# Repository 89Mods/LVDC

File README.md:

# LVDC
Replica of the [Launch Vehicle Digital Computer](https://www.ibiblio.org/apollo/LVDC.html) using 74-series logic. This projects only aims to keep the CPU Architecture binary-compatible with the original. Implementation details, IO Peripherals and Software are all originally created by me. This is party due to the fact that detailed hardware descriptions (i.e. schematics) are not as abundant for the LVDC as for the AGC, but also because this project doubled as a challenge to myself to implement such an odd instruction set, but using every trick I’ve learned from my years of engineering integrated circuit layouts. It turns out that applying nanoscale engineering tricks to a macroscale discrete logic build can work out quite well. The clock speed of this computer is 2.5MHz, but it can probably go faster.

This LVDC is accurate to the original in the sense that it executes the same instructions that function the exact same, has the same memory layout (including special locations like HOP save and MQ) and can execute snippets of original LVDC code.

The differences are:
  - This computer is parallel and not bit-serial, and is also microcoded
  - It is implemented using 74-series logic and not discrete transistors (I wish to be able to take it with me to events, so it couldn’t get too big)
  - Everything hooked up to the PIO (IO read/write) instruction is my own invention, with the exception of the the interrupt latch clear IO location, which it shares with the original LVDC
  - Instruction cycles times are much faster, probably on an order of magnitude or more
  - The hardware multiply/divide circuitry (as designed so far) does NOT share the inacuracies in low-order bits as the original LVDC, instead always producing the 100% correct result

Infact, I took the most liberties with the IO Card, which contains various modern components hooked into the CPU’s IO Bus. Its mostly a random mashup of things I thought would be cool (there is even a Commodore SID replica in there) to demonstrate the computer with.

The most significant addition is that of a front panel (the original LVDC was an embedded device with no user interface) which is a bit like a DSKY, but stripped down and only capable of displaying in hexadecimal. The panel is optional. I can be safely removed and the computer used as a true embedded device.

Software wise, things are still WiP. Two ROMs provide just enough storage for a small bootloader to initialize the entire SRAM from a flash IC. Sadly, core memory is far too bulky and expensive, so this will have to do. I created a mini-OS for this system that allows a user to control the computer by typing in commands consisting of a Noun and Verb into the keypad.

**Known Issues:**
  - The HOP Save feature is bugged. The Instruction Pointer in the stored value is off by one. Trying to return with it will return execution to the transfer or HOP instruction that started the subroutine call, not the one following it, triggering an infinite loop. Fixed for now in software by modifying the saved value before return.
  - While all schematic files have been updated with fixes to additional problems discovered post-production, the schematic layout for the Control board still need to be redone.
  - The EXM instruction has only been minimally tested because I don’t understand how it is useful (thing takes up half a dozen ICs just to handle weird edge cases caused by it and I’m still left scratching my head on how I’m supposed to use it).
  - The hardware multiply/divide functionality has yet to be physically implemented. In `LVDC.circ` you can see that I have designed it, but I’ve yet to translate this to a PCB design because I couldn’t get it made yet anyways (its the most expensive part of the whole computer).
  - The interrupt logic sometimes does not reset properly and I don’t understand why

# Repository Structure

`LVDC.circ` is where I prototyped the logic design using Logisim Evolution, but it is quite bugged and now far outdated.

`microcode_gen.c` is the C program that spits out the raw binary images for the microcode ROMs from a more high-level description.

`KiCad` is where the schematics and PCB layouts live. Related to this is `CPLD`, which holds the HDL code for the CPLD on the GPIO PCB.

`Bench` is the result of using [KiCadVerilog](https://github.com/89Mods/KiCadVerilog) to automatically extract Verilog netlists out of the KiCad schematic files and using them to build a simulation of the computer for verification purposes before starting physical production. This is quite a novel approach and I used it here for the first time.

`behavioral` contains a Behavioral Verilog model of the LVDC I used as a starting point. It is incredibly inaccurate as I have not updated it in same time.

`Programs` contains the software I’m writing for this computer. Currently just the Bootloader source and the WiP mini-OS mentioned earlier. [My fork of the AS Macroassembler](https://github.com/AvalonSemiconductors/asl-avalonsemi/) has support for the LVDC, and this is used to assemble all LVDC code in this directory.

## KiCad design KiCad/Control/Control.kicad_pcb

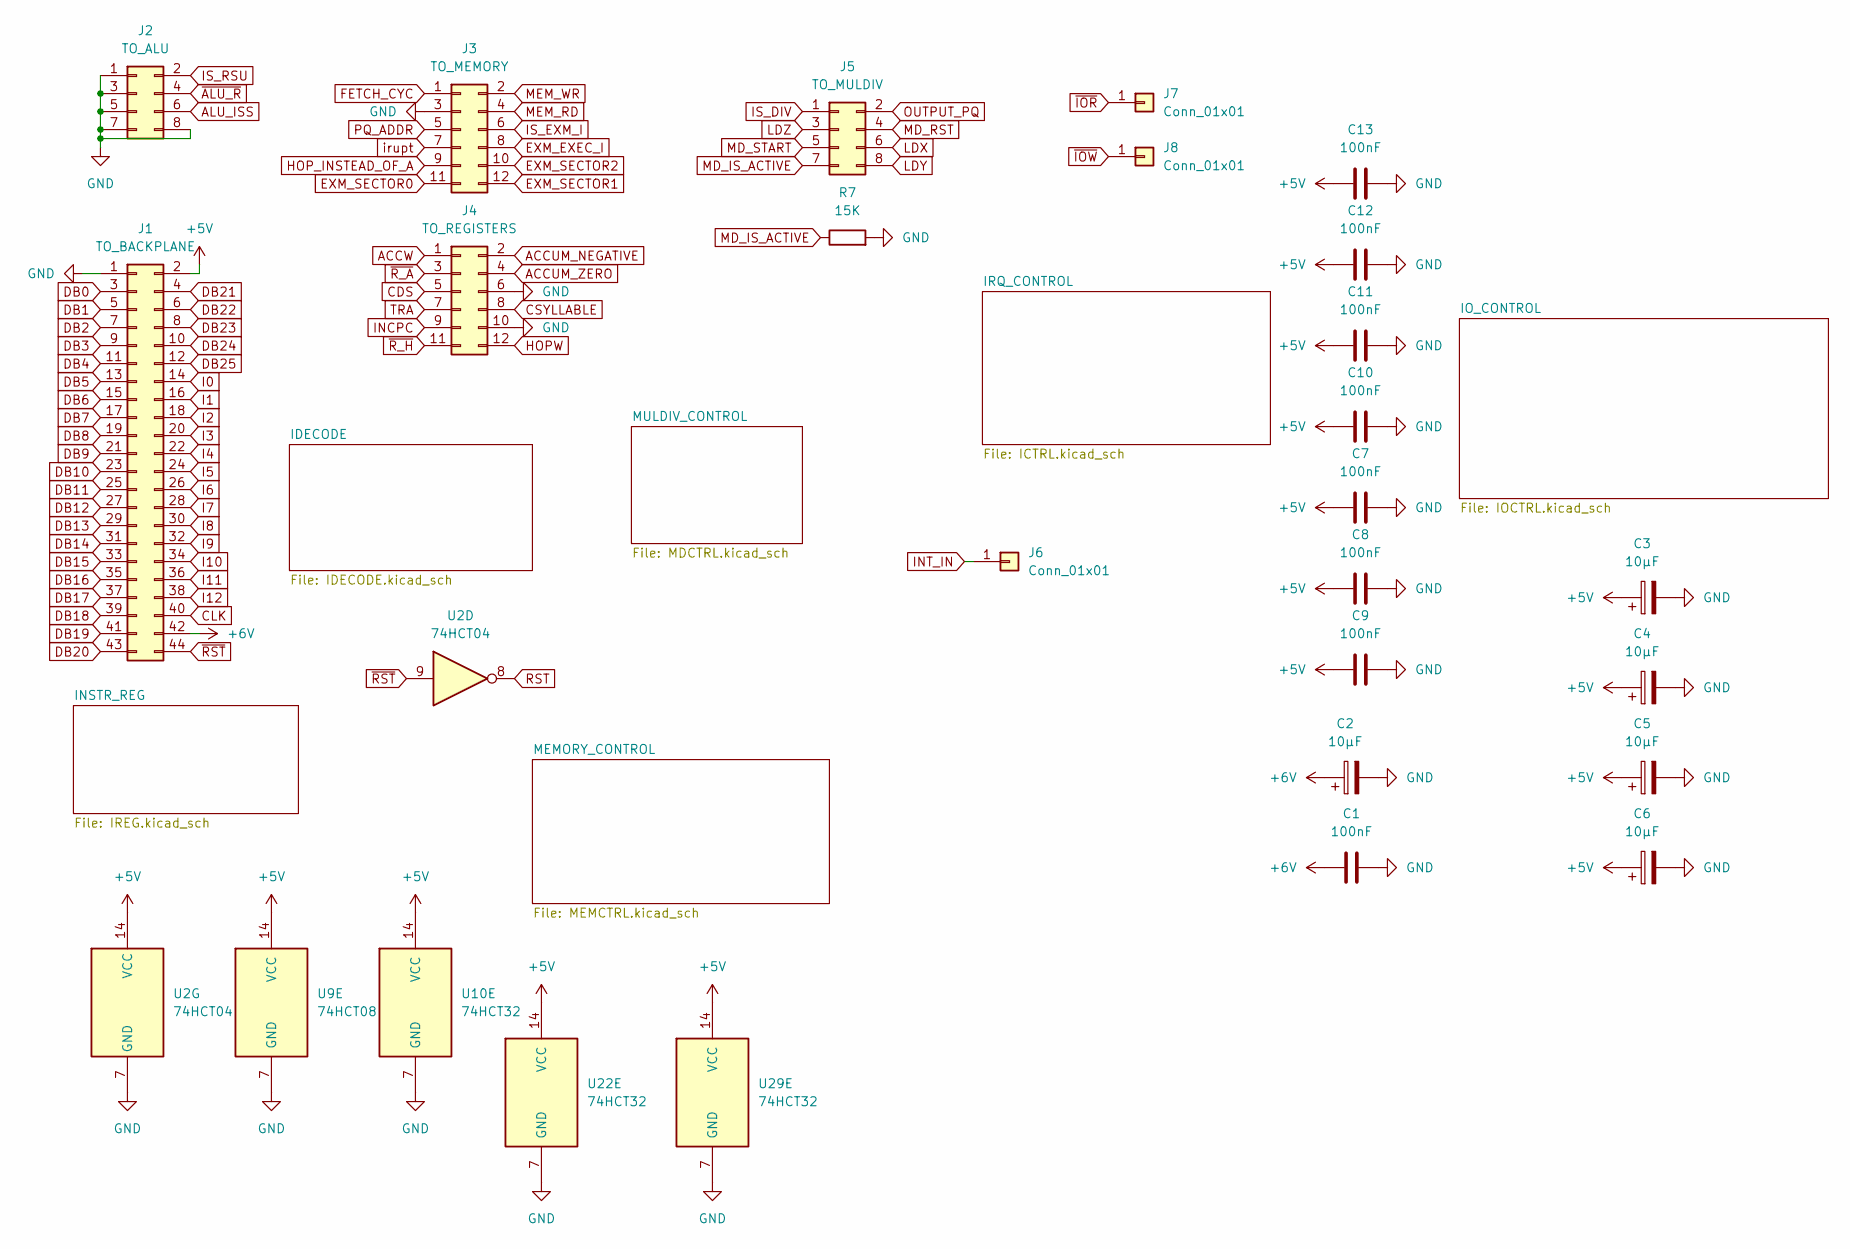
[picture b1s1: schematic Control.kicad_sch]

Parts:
C1, C7, C8, C9, C10, C11, C12, C13: 100nF; C_0805_2012Metric_Pad1.18x1.45mm_HandSolder
C2, C3, C4, C5, C6: 10µF; CP_Radial_D4.0mm_P2.00mm
J1: TO_BACKPLANE; PinHeader_2x22_P2.54mm_Vertical
J2: TO_ALU; PinHeader_2x04_P2.54mm_Vertical
J3: TO_MEMORY; PinHeader_2x06_P2.54mm_Vertical
J4: TO_REGISTERS; PinHeader_2x06_P2.54mm_Vertical
J5: TO_MULDIV; PinHeader_2x04_P2.54mm_Vertical
J6, J7, J8: Conn_01x01; PinHeader_1x01_P2.54mm_Vertical
R7: 15K; R_1206_3216Metric_Pad1.30x1.75mm_HandSolder
U2: 74HCT04; SO-14_3.9x8.65mm_P1.27mm
U9: 74HCT08; SO-14_3.9x8.65mm_P1.27mm
U10, U22, U29: 74HCT32; SO-14_3.9x8.65mm_P1.27mm

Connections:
+5V: C3.1, C4.1, C5.1, C6.1, C7.1, C8.1, C9.1, C10.1, C11.1, C12.1, C13.1, J1.2, U2.14 (VCC), U9.14 (VCC), U10.14 (VCC), U22.14 (VCC), U29.14 (VCC); also elsewhere on the board
+6V: C1.1, C2.1, J1.42; also elsewhere on the board
ACCUM_NEGATIVE: J4.2; also elsewhere on the board
ACCUM_ZERO: J4.4; also elsewhere on the board
ACCW: J4.1; also elsewhere on the board
ALU_ISS: J2.6; also elsewhere on the board
CDS: J4.5; also elsewhere on the board
CLK: J1.40; also elsewhere on the board
CSYLLABLE: J4.8; also elsewhere on the board
DB0: J1.3; also elsewhere on the board
DB1: J1.5; also elsewhere on the board
DB2: J1.7; also elsewhere on the board
DB3: J1.9; also elsewhere on the board
DB4: J1.11; also elsewhere on the board
DB5: J1.13; also elsewhere on the board
DB6: J1.15; also elsewhere on the board
DB7: J1.17; also elsewhere on the board
DB8: J1.19; also elsewhere on the board
DB9: J1.21; also elsewhere on the board
DB10: J1.23; also elsewhere on the board
DB11: J1.25; also elsewhere on the board
DB12: J1.27; also elsewhere on the board
DB13: J1.29; also elsewhere on the board
DB14: J1.31; also elsewhere on the board
DB15: J1.33; also elsewhere on the board
DB16: J1.35; also elsewhere on the board
DB17: J1.37; also elsewhere on the board
DB18: J1.39; also elsewhere on the board
DB19: J1.41; also elsewhere on the board
DB20: J1.43; also elsewhere on the board
DB21: J1.4; also elsewhere on the board
DB22: J1.6; also elsewhere on the board
DB23: J1.8; also elsewhere on the board
DB24: J1.10; also elsewhere on the board
DB25: J1.12; also elsewhere on the board
EXM_EXEC_I: J3.8; also elsewhere on the board
EXM_SECTOR0: J3.11; also elsewhere on the board
EXM_SECTOR1: J3.12; also elsewhere on the board
EXM_SECTOR2: J3.10; also elsewhere on the board
FETCH_CYC: J3.1; also elsewhere on the board
GND: C1.2, C2.2, C3.2, C4.2, C5.2, C6.2, C7.2, C8.2, C9.2, C10.2, C11.2, C12.2, C13.2, J1.1, J2.1, J2.3, J2.5, J2.7, J2.8, J3.3, J4.6, J4.10, R7.2, U2.7 (GND), U9.7 (GND), U10.7 (GND), U22.7 (GND), U29.7 (GND); also elsewhere on the board
HOPW: J4.12; also elsewhere on the board
HOP_INSTEAD_OF_A: J3.9; also elsewhere on the board
I0: J1.14; also elsewhere on the board
I1: J1.16; also elsewhere on the board
I2: J1.18; also elsewhere on the board
I3: J1.20; also elsewhere on the board
I4: J1.22; also elsewhere on the board
I5: J1.24; also elsewhere on the board
I6: J1.26; also elsewhere on the board
I7: J1.28; also elsewhere on the board
I8: J1.30; also elsewhere on the board
I9: J1.32; also elsewhere on the board
I10: J1.34; also elsewhere on the board
I11: J1.36; also elsewhere on the board
I12: J1.38; also elsewhere on the board
INCPC: J4.9; also elsewhere on the board
INT_IN: J6.1; also elsewhere on the board
IS_DIV: J5.1; also elsewhere on the board
IS_EXM_I: J3.6; also elsewhere on the board
IS_RSU: J2.2; also elsewhere on the board
LDX: J5.6; also elsewhere on the board
LDY: J5.8; also elsewhere on the board
LDZ: J5.3; also elsewhere on the board
MD_IS_ACTIVE: J5.7, R7.1; also elsewhere on the board
MD_RST: J5.4; also elsewhere on the board
MD_START: J5.5; also elsewhere on the board
MEM_RD: J3.4; also elsewhere on the board
MEM_WR: J3.2; also elsewhere on the board
OUTPUT_PQ: J5.2; also elsewhere on the board
PQ_ADDR: J3.5; also elsewhere on the board
RST: U2.8; also elsewhere on the board
TRA: J4.7; also elsewhere on the board
irupt: J3.7; also elsewhere on the board
~ALU_R: J2.4; also elsewhere on the board
~IOR: J7.1; also elsewhere on the board
~IOW: J8.1; also elsewhere on the board
~RST: J1.44, U2.9; also elsewhere on the board
~R_A: J4.3; also elsewhere on the board
~R_H: J4.11; also elsewhere on the board

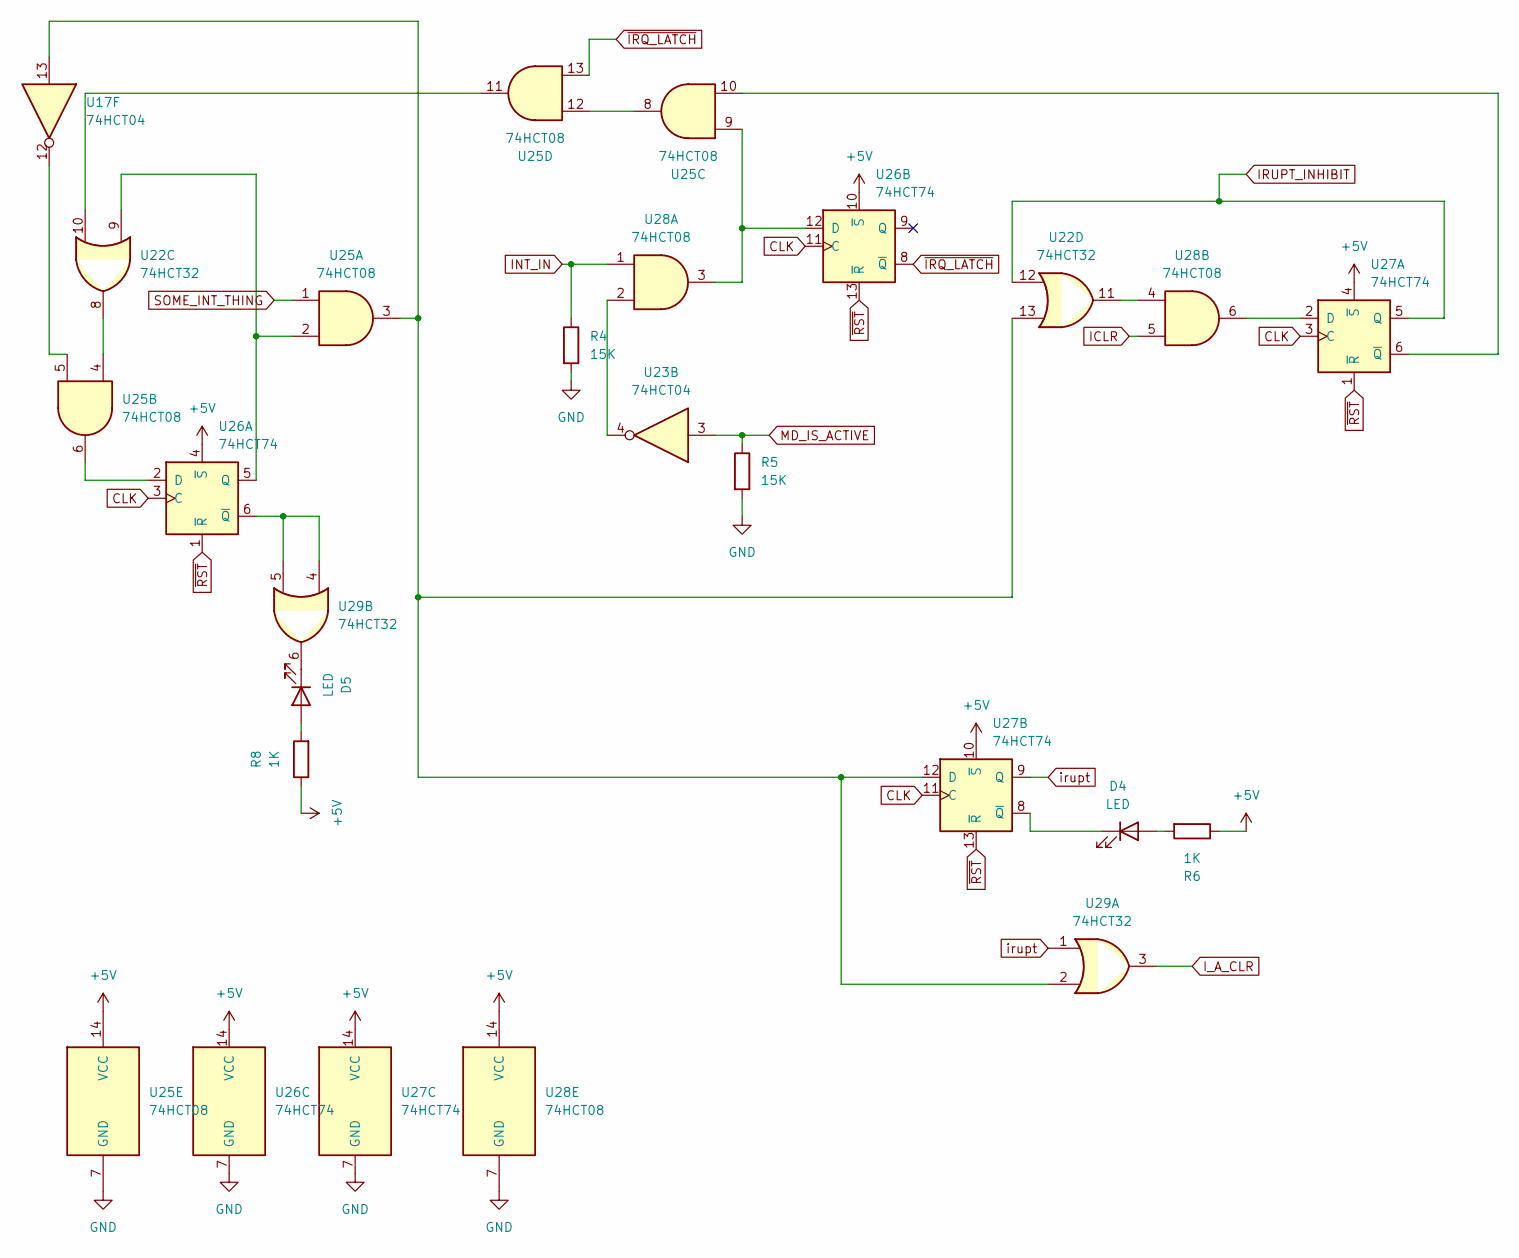
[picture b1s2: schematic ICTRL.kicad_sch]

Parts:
D4, D5: LED; LED_1206_3216Metric_Pad1.42x1.75mm_HandSolder
R4, R5: 15K; R_1206_3216Metric_Pad1.30x1.75mm_HandSolder
R6, R8: 1K; R_1206_3216Metric_Pad1.30x1.75mm_HandSolder
U17, U23: 74HCT04; SO-14_3.9x8.65mm_P1.27mm
U22, U29: 74HCT32; SO-14_3.9x8.65mm_P1.27mm
U25, U28: 74HCT08; SO-14_3.9x8.65mm_P1.27mm
U26, U27: 74HCT74; SO-14_3.9x8.65mm_P1.27mm

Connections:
+5V: R6.1, R8.1, U25.14 (VCC), U26.4 (~S), U26.10 (~S), U26.14 (VCC), U27.4 (~S), U27.10 (~S), U27.14 (VCC), U28.14 (VCC); also elsewhere on the board
CLK: U26.3 (C), U26.11 (C), U27.3 (C), U27.11 (C); also elsewhere on the board
GND: R4.2, R5.2, U25.7 (GND), U26.7 (GND), U27.7 (GND), U28.7 (GND); also elsewhere on the board
ICLR: U28.5; also elsewhere on the board
INT_IN: R4.1, U28.1; also elsewhere on the board
IRUPT_INHIBIT: U22.12, U27.5 (Q)
I_A_CLR: U29.3; also elsewhere on the board
MD_IS_ACTIVE: R5.1, U23.3; also elsewhere on the board
unnamed: D4.2 (A), R6.2
unnamed: D4.1 (K), U27.8 (~Q)
unnamed: D5.2 (A), R8.2
unnamed: D5.1 (K), U29.6
unnamed: U17.12, U25.5
unnamed: U22.8, U25.4
unnamed: U22.10, U25.11
unnamed: U22.11, U28.4
unnamed: U23.4, U28.2
unnamed: U25.8, U25.12
unnamed: U25.6, U26.2 (D)
unnamed: U22.9, U25.2, U26.5 (Q)
unnamed: U26.6 (~Q), U29.4, U29.5
unnamed: U25.9, U26.12 (D), U28.3
unnamed: U27.2 (D), U28.6
unnamed: U25.10, U27.6 (~Q)
unnamed: U17.13, U22.13, U25.3, U27.12 (D), U29.2
SOME_INT_THING: U25.1; also elsewhere on the board
irupt: U27.9 (Q), U29.1; also elsewhere on the board
~IRQ_LATCH: U25.13, U26.8 (~Q)
~RST: U26.1 (~R), U26.13 (~R), U27.1 (~R), U27.13 (~R); also elsewhere on the board

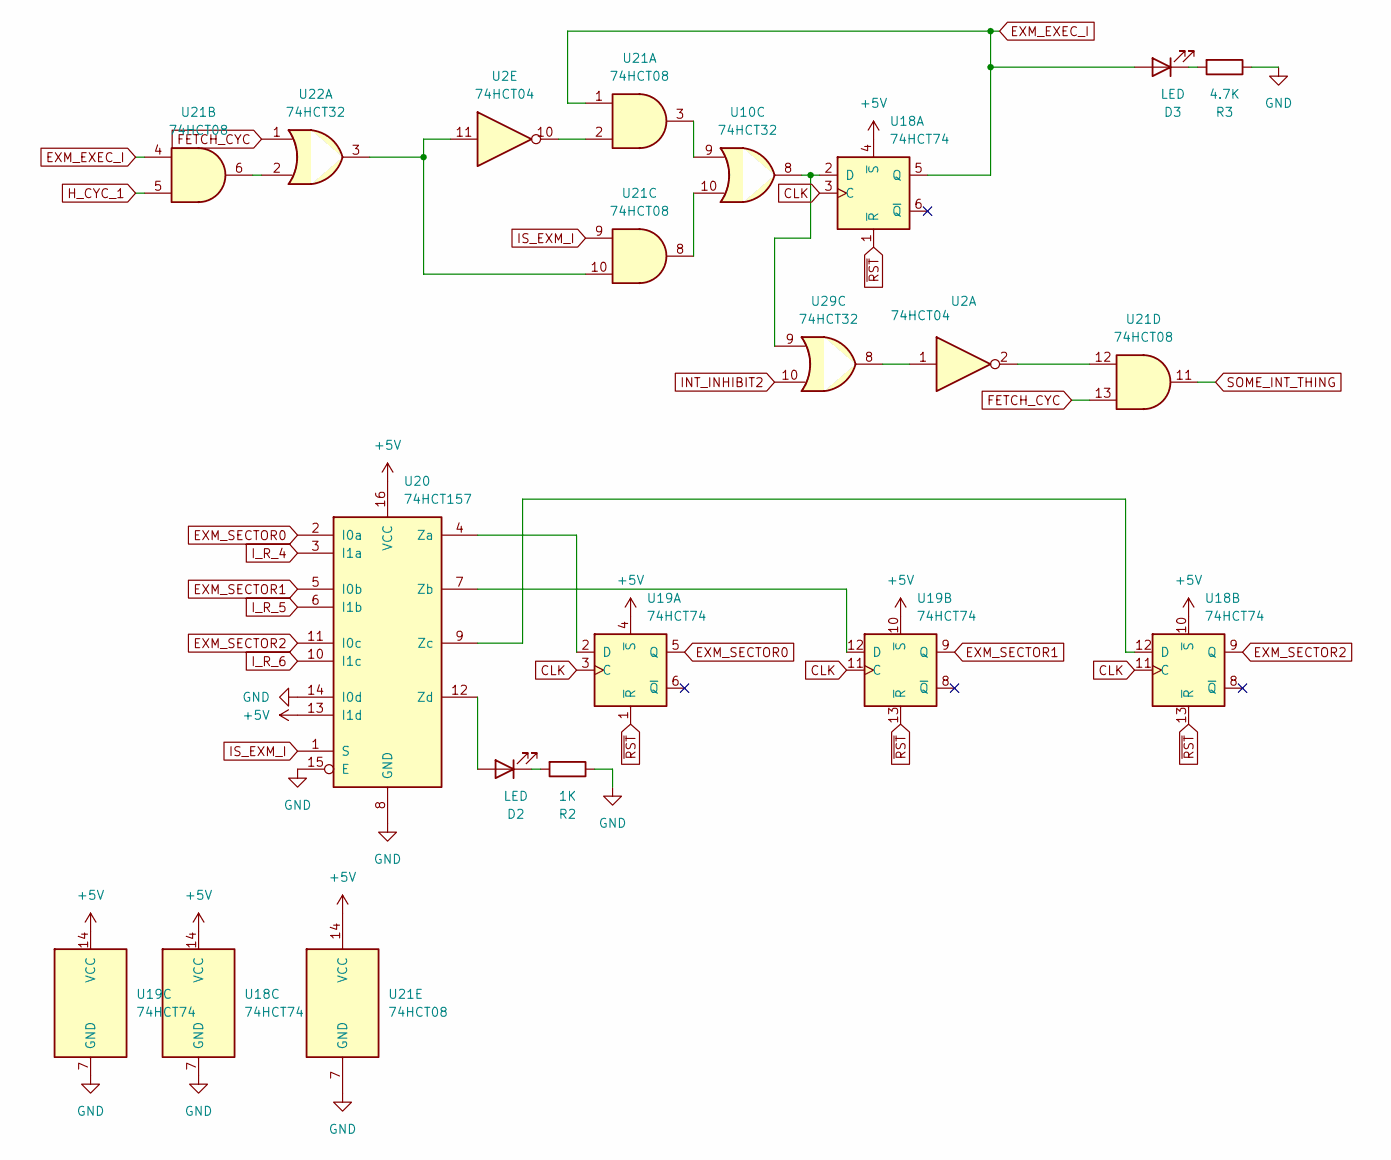
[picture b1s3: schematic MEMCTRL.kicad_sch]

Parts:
D2, D3: LED; LED_1206_3216Metric_Pad1.42x1.75mm_HandSolder
R2: 1K; R_1206_3216Metric_Pad1.30x1.75mm_HandSolder
R3: 4.7K; R_1206_3216Metric_Pad1.30x1.75mm_HandSolder
U2: 74HCT04; SO-14_3.9x8.65mm_P1.27mm
U10, U22, U29: 74HCT32; SO-14_3.9x8.65mm_P1.27mm
U18, U19: 74HCT74; SO-14_3.9x8.65mm_P1.27mm
U20: 74HCT157; SO-16_3.9x9.9mm_P1.27mm
U21: 74HCT08; SO-14_3.9x8.65mm_P1.27mm

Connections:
+5V: U18.4 (~S), U18.10 (~S), U18.14 (VCC), U19.4 (~S), U19.10 (~S), U19.14 (VCC), U20.13 (I1d), U20.16 (VCC), U21.14 (VCC); also elsewhere on the board
CLK: U18.3 (C), U18.11 (C), U19.3 (C), U19.11 (C); also elsewhere on the board
EXM_EXEC_I: D3.2 (A), U18.5 (Q), U21.1, U21.4; also elsewhere on the board
EXM_SECTOR0: U19.5 (Q), U20.2 (I0a); also elsewhere on the board
EXM_SECTOR1: U19.9 (Q), U20.5 (I0b); also elsewhere on the board
EXM_SECTOR2: U18.9 (Q), U20.11 (I0c); also elsewhere on the board
FETCH_CYC: U21.13, U22.1; also elsewhere on the board
GND: R2.1, R3.1, U18.7 (GND), U19.7 (GND), U20.8 (GND), U20.14 (I0d), U20.15 (E), U21.7 (GND); also elsewhere on the board
H_CYC_1: U21.5; also elsewhere on the board
INT_INHIBIT2: U29.10; also elsewhere on the board
IS_EXM_I: U20.1 (S), U21.9; also elsewhere on the board
I_R_4: U20.3 (I1a); also elsewhere on the board
I_R_5: U20.6 (I1b); also elsewhere on the board
I_R_6: U20.10 (I1c); also elsewhere on the board
unnamed: D2.2 (A), U20.12 (Zd)
unnamed: D2.1 (K), R2.2
unnamed: D3.1 (K), R3.2
unnamed: U2.1, U29.8
unnamed: U2.2, U21.12
unnamed: U2.10, U21.2
unnamed: U2.11, U21.10, U22.3
unnamed: U10.9, U21.3
unnamed: U10.10, U21.8
unnamed: U10.8, U18.2 (D), U29.9
unnamed: U18.12 (D), U20.9 (Zc)
unnamed: U19.2 (D), U20.4 (Za)
unnamed: U19.12 (D), U20.7 (Zb)
unnamed: U21.6, U22.2
SOME_INT_THING: U21.11; also elsewhere on the board
~RST: U18.1 (~R), U18.13 (~R), U19.1 (~R), U19.13 (~R); also elsewhere on the board

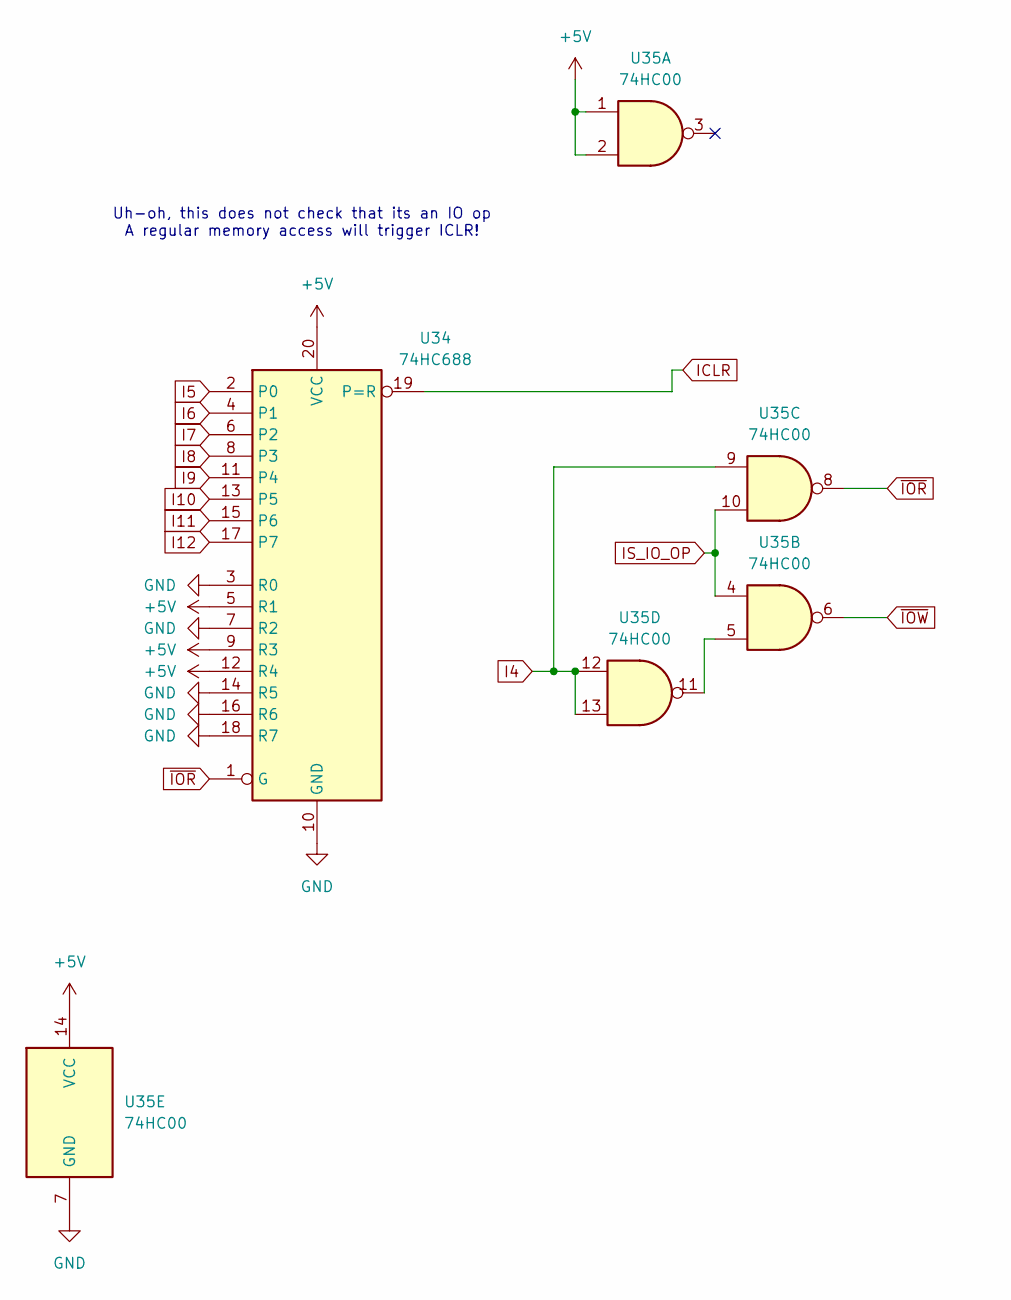
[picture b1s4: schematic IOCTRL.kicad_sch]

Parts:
U34: 74HC688; SO-20_12.8x7.5mm_P1.27mm
U35: 74HC00; SO-14_3.9x8.65mm_P1.27mm

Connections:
+5V: U34.5 (R1), U34.9 (R3), U34.12 (R4), U34.20 (VCC), U35.1, U35.2, U35.14 (VCC); also elsewhere on the board
GND: U34.3 (R0), U34.7 (R2), U34.10 (GND), U34.14 (R5), U34.16 (R6), U34.18 (R7), U35.7 (GND); also elsewhere on the board
I4: U35.9, U35.12, U35.13; also elsewhere on the board
I5: U34.2 (P0); also elsewhere on the board
I6: U34.4 (P1); also elsewhere on the board
I7: U34.6 (P2); also elsewhere on the board
I8: U34.8 (P3); also elsewhere on the board
I9: U34.11 (P4); also elsewhere on the board
I10: U34.13 (P5); also elsewhere on the board
I11: U34.15 (P6); also elsewhere on the board
I12: U34.17 (P7); also elsewhere on the board
ICLR: U34.19 (P=R); also elsewhere on the board
IS_IO_OP: U35.4, U35.10; also elsewhere on the board
unnamed: U35.5, U35.11
~IOR: U34.1 (G), U35.8; also elsewhere on the board
~IOW: U35.6; also elsewhere on the board

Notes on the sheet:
Uh-oh, this does not check that its an IO op A regular memory access will trigger ICLR!

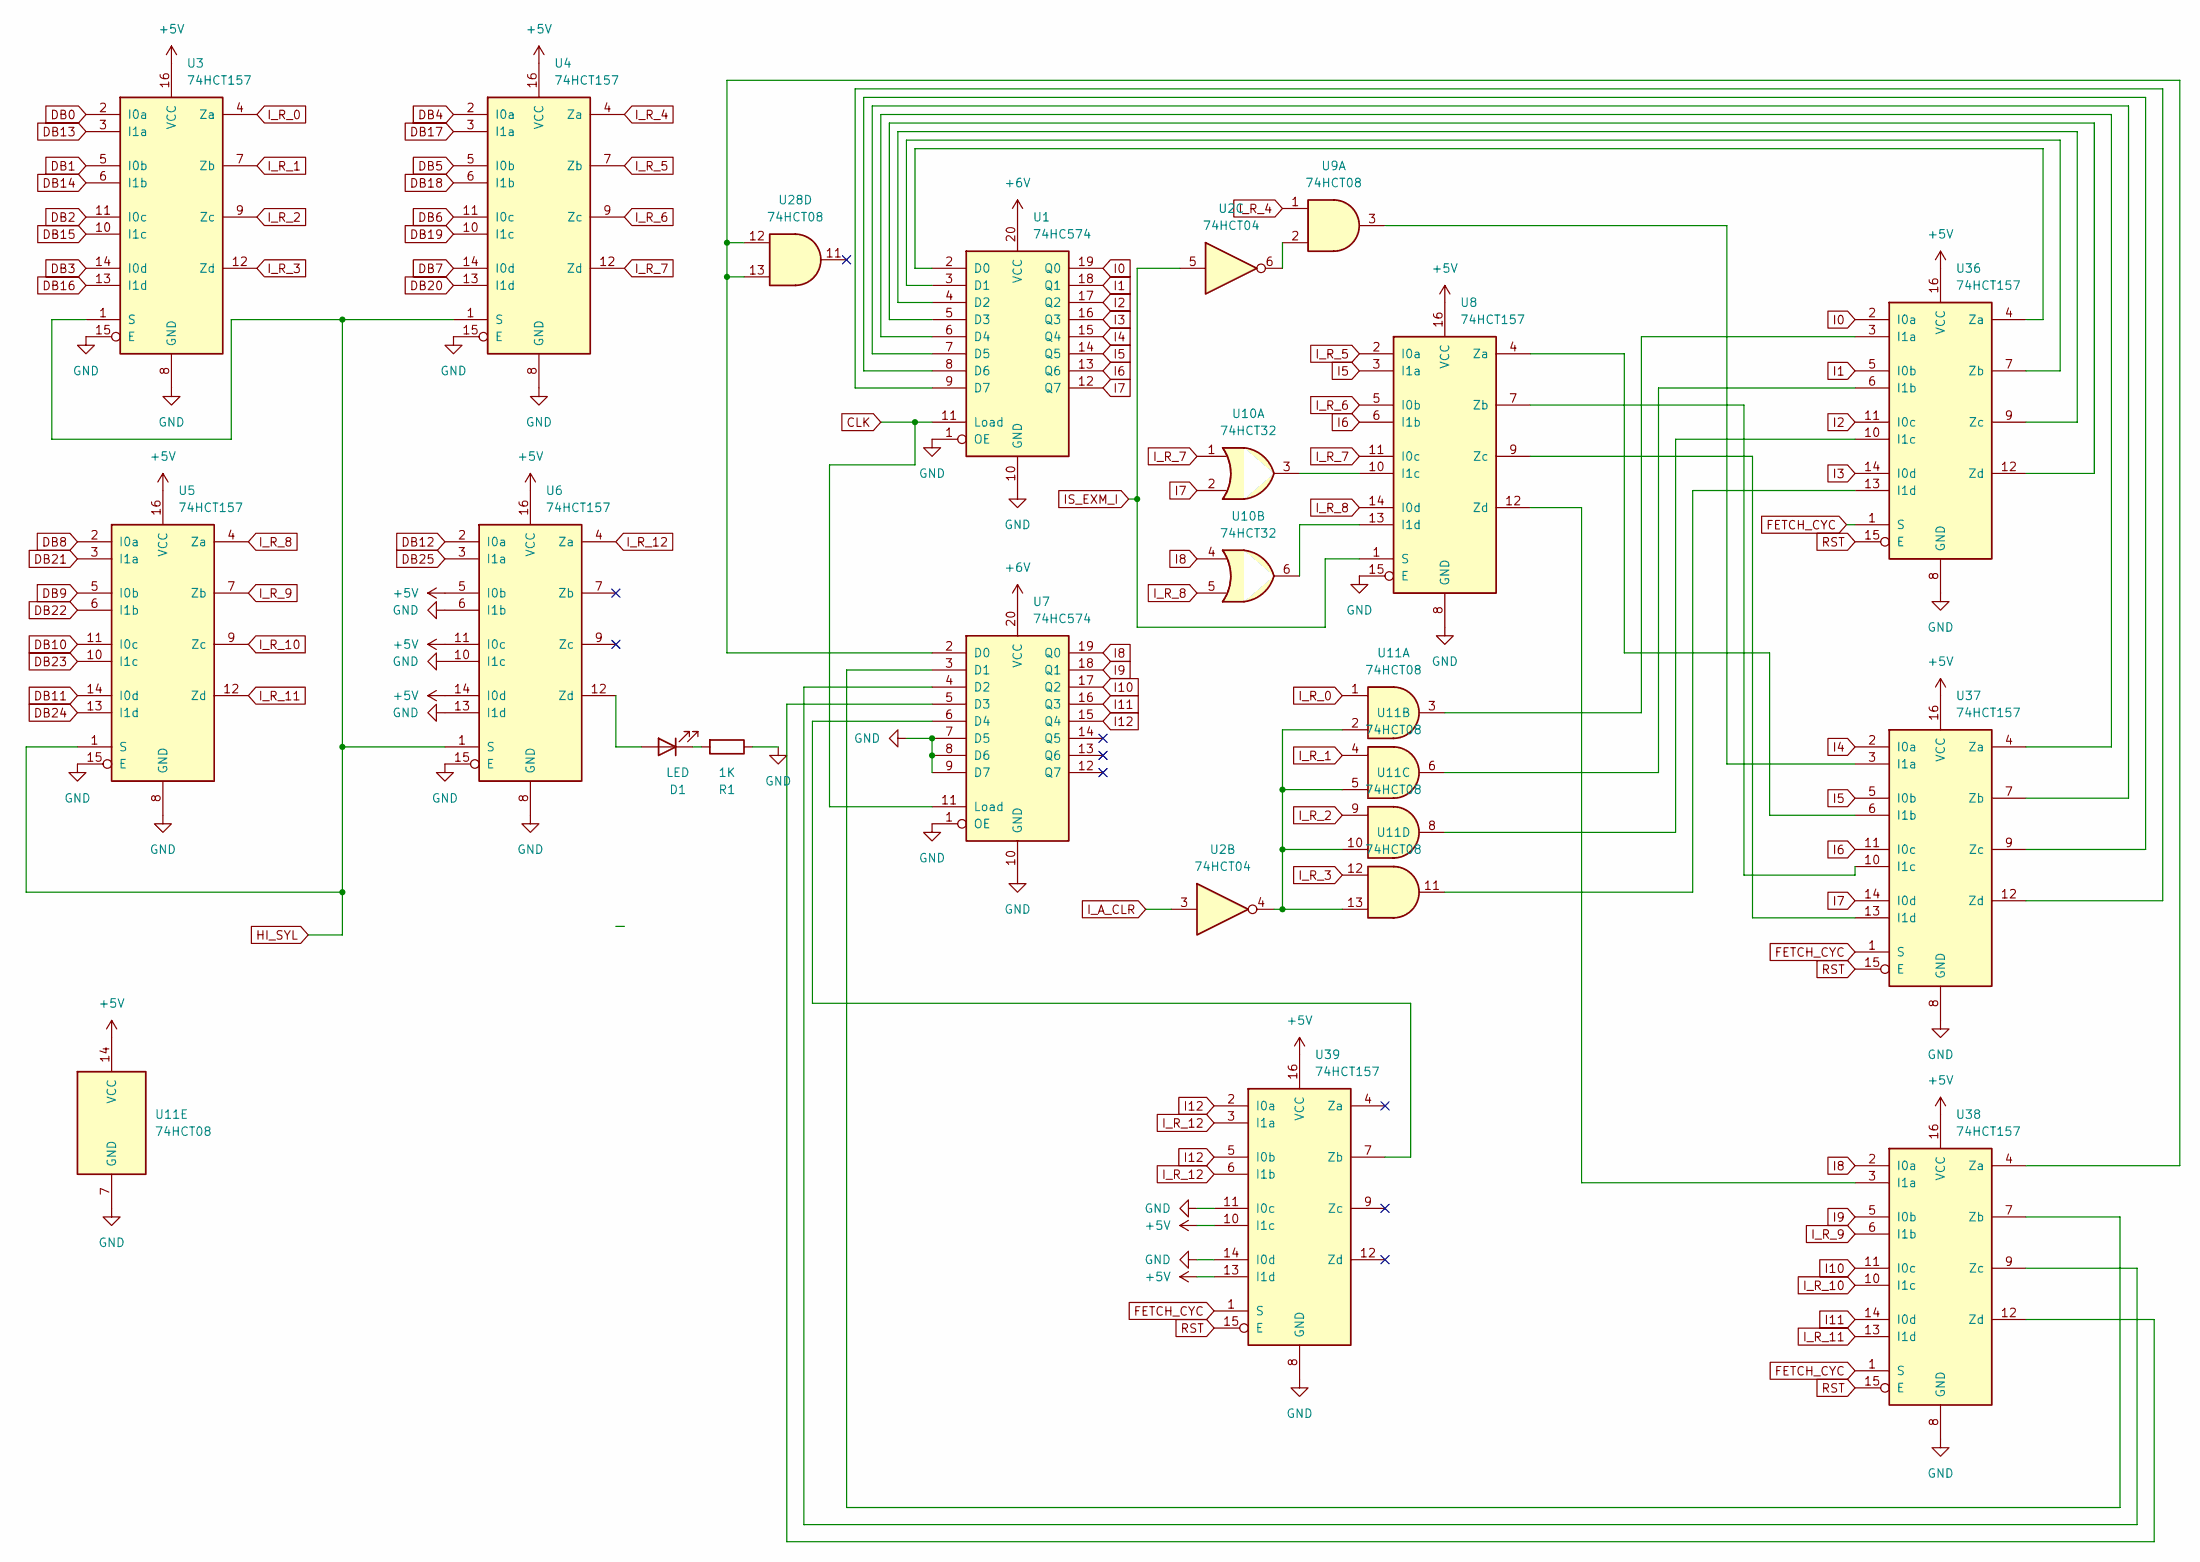
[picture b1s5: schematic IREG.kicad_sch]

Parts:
D1: LED; LED_1206_3216Metric_Pad1.42x1.75mm_HandSolder
R1: 1K; R_1206_3216Metric_Pad1.30x1.75mm_HandSolder
U1, U7: 74HC574; SO-20_12.8x7.5mm_P1.27mm
U2: 74HCT04; SO-14_3.9x8.65mm_P1.27mm
U3, U4, U5, U6, U8, U36, U37, U38, U39: 74HCT157; SO-16_3.9x9.9mm_P1.27mm
U9, U11, U28: 74HCT08; SO-14_3.9x8.65mm_P1.27mm
U10: 74HCT32; SO-14_3.9x8.65mm_P1.27mm

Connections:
+5V: U3.16 (VCC), U4.16 (VCC), U5.16 (VCC), U6.5 (I0b), U6.11 (I0c), U6.14 (I0d), U6.16 (VCC), U8.16 (VCC), U11.14 (VCC), U36.16 (VCC), U37.16 (VCC), U38.16 (VCC), U39.10 (I1c), U39.13 (I1d), U39.16 (VCC); also elsewhere on the board
+6V: U1.20 (VCC), U7.20 (VCC); also elsewhere on the board
CLK: U1.11 (Load), U7.11 (Load); also elsewhere on the board
DB0: U3.2 (I0a); also elsewhere on the board
DB1: U3.5 (I0b); also elsewhere on the board
DB2: U3.11 (I0c); also elsewhere on the board
DB3: U3.14 (I0d); also elsewhere on the board
DB4: U4.2 (I0a); also elsewhere on the board
DB5: U4.5 (I0b); also elsewhere on the board
DB6: U4.11 (I0c); also elsewhere on the board
DB7: U4.14 (I0d); also elsewhere on the board
DB8: U5.2 (I0a); also elsewhere on the board
DB9: U5.5 (I0b); also elsewhere on the board
DB10: U5.11 (I0c); also elsewhere on the board
DB11: U5.14 (I0d); also elsewhere on the board
DB12: U6.2 (I0a); also elsewhere on the board
DB13: U3.3 (I1a); also elsewhere on the board
DB14: U3.6 (I1b); also elsewhere on the board
DB15: U3.10 (I1c); also elsewhere on the board
DB16: U3.13 (I1d); also elsewhere on the board
DB17: U4.3 (I1a); also elsewhere on the board
DB18: U4.6 (I1b); also elsewhere on the board
DB19: U4.10 (I1c); also elsewhere on the board
DB20: U4.13 (I1d); also elsewhere on the board
DB21: U5.3 (I1a); also elsewhere on the board
DB22: U5.6 (I1b); also elsewhere on the board
DB23: U5.10 (I1c); also elsewhere on the board
DB24: U5.13 (I1d); also elsewhere on the board
DB25: U6.3 (I1a); also elsewhere on the board
FETCH_CYC: U36.1 (S), U37.1 (S), U38.1 (S), U39.1 (S); also elsewhere on the board
GND: R1.1, U1.1 (OE), U1.10 (GND), U3.8 (GND), U3.15 (E), U4.8 (GND), U4.15 (E), U5.8 (GND), U5.15 (E), U6.6 (I1b), U6.8 (GND), U6.10 (I1c), U6.13 (I1d), U6.15 (E), U7.1 (OE), U7.7 (D5), U7.8 (D6), U7.9 (D7), U7.10 (GND), U8.8 (GND), U8.15 (E), U11.7 (GND), U36.8 (GND), U37.8 (GND), U38.8 (GND), U39.8 (GND), U39.11 (I0c), U39.14 (I0d); also elsewhere on the board
HI_SYL: U3.1 (S), U4.1 (S), U5.1 (S), U6.1 (S); also elsewhere on the board
I0: U1.19 (Q0), U36.2 (I0a); also elsewhere on the board
I1: U1.18 (Q1), U36.5 (I0b); also elsewhere on the board
I2: U1.17 (Q2), U36.11 (I0c); also elsewhere on the board
I3: U1.16 (Q3), U36.14 (I0d); also elsewhere on the board
I4: U1.15 (Q4), U37.2 (I0a); also elsewhere on the board
I5: U1.14 (Q5), U8.3 (I1a), U37.5 (I0b); also elsewhere on the board
I6: U1.13 (Q6), U8.6 (I1b), U37.11 (I0c); also elsewhere on the board
I7: U1.12 (Q7), U10.2, U37.14 (I0d); also elsewhere on the board
I8: U7.19 (Q0), U10.4, U38.2 (I0a); also elsewhere on the board
I9: U7.18 (Q1), U38.5 (I0b); also elsewhere on the board
I10: U7.17 (Q2), U38.11 (I0c); also elsewhere on the board
I11: U7.16 (Q3), U38.14 (I0d); also elsewhere on the board
I12: U7.15 (Q4), U39.2 (I0a), U39.5 (I0b); also elsewhere on the board
IS_EXM_I: U2.5, U8.1 (S); also elsewhere on the board
I_A_CLR: U2.3; also elsewhere on the board
I_R_0: U3.4 (Za), U11.1
I_R_1: U3.7 (Zb), U11.4
I_R_2: U3.9 (Zc), U11.9
I_R_3: U3.12 (Zd), U11.12
I_R_4: U4.4 (Za), U9.1; also elsewhere on the board
I_R_5: U4.7 (Zb), U8.2 (I0a); also elsewhere on the board
I_R_6: U4.9 (Zc), U8.5 (I0b); also elsewhere on the board
I_R_7: U4.12 (Zd), U8.11 (I0c), U10.1
I_R_8: U5.4 (Za), U8.14 (I0d), U10.5
I_R_9: U5.7 (Zb), U38.6 (I1b)
I_R_10: U5.9 (Zc), U38.10 (I1c)
I_R_11: U5.12 (Zd), U38.13 (I1d)
I_R_12: U6.4 (Za), U39.3 (I1a), U39.6 (I1b)
unnamed: D1.2 (A), U6.12 (Zd)
unnamed: D1.1 (K), R1.2
unnamed: U1.2 (D0), U36.4 (Za)
unnamed: U1.3 (D1), U36.7 (Zb)
unnamed: U1.4 (D2), U36.9 (Zc)
unnamed: U1.5 (D3), U36.12 (Zd)
unnamed: U1.6 (D4), U37.4 (Za)
unnamed: U1.7 (D5), U37.7 (Zb)
unnamed: U1.8 (D6), U37.9 (Zc)
unnamed: U1.9 (D7), U37.12 (Zd)
unnamed: U2.6, U9.2
unnamed: U8.10 (I1c), U10.3
unnamed: U8.13 (I1d), U10.6
unnamed: U2.4, U11.2, U11.5, U11.10, U11.13
unnamed: U11.3, U36.3 (I1a)
unnamed: U11.6, U36.6 (I1b)
unnamed: U11.8, U36.10 (I1c)
unnamed: U11.11, U36.13 (I1d)
unnamed: U9.3, U37.3 (I1a)
unnamed: U8.4 (Za), U37.6 (I1b)
unnamed: U8.7 (Zb), U37.10 (I1c)
unnamed: U8.9 (Zc), U37.13 (I1d)
unnamed: U8.12 (Zd), U38.3 (I1a)
unnamed: U7.2 (D0), U28.12, U28.13, U38.4 (Za)
unnamed: U7.3 (D1), U38.7 (Zb)
unnamed: U7.4 (D2), U38.9 (Zc)
unnamed: U7.5 (D3), U38.12 (Zd)
unnamed: U7.6 (D4), U39.7 (Zb)
RST: U36.15 (E), U37.15 (E), U38.15 (E), U39.15 (E); also elsewhere on the board
